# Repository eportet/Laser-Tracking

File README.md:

# Laser-Tracking

Code
====

Three folders in this directory:
* CameraTracking: Contains code that does corse tracking on RasPi
* Transmitter: Contains code that runs on photon plugged inito receiver PCBs
* Receiver: Contains code that runs on photon controlling servos and MEMS

Flashing Photon Code
====================

* Download Particle CLI on Mac or Linux. See Particle help for details.
* Place Photon in DFU mode by holding down both buttons, release Setup button. Light should blink purple, continue to hold the Reset button until light blinks yellow.
* Run ```particle photon compile --saveTo out.bin .``` in directory with *.ino file.
* Run ```particle flash --usb out.bin```
* When program is running, particle light should be constant white. If the light blinks green or blue, something is wrong, check that system mode is set to manual in code and that photon firmware is up to date.

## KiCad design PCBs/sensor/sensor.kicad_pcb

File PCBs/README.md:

# PCBs for laser tracking
We've got two PCBs to make the sensor for the drone.
The **sensor** board holds 24 photodiodes and sticks the info on a 26-pin header. The outputs require pullup resistors.
The **mux** board attaches to the sensor board, and is also designed to hold a particle photon and a RF communication module.

The kicad files, digikey bill of materials, and gerbers are in each of the directories. BOM for 3 boards + a spare, which is the minumum oshpark order.
We printed both boards with oshpark and it worked out well enough. "Sensor" is on 2oz copper, "mux" is standard.

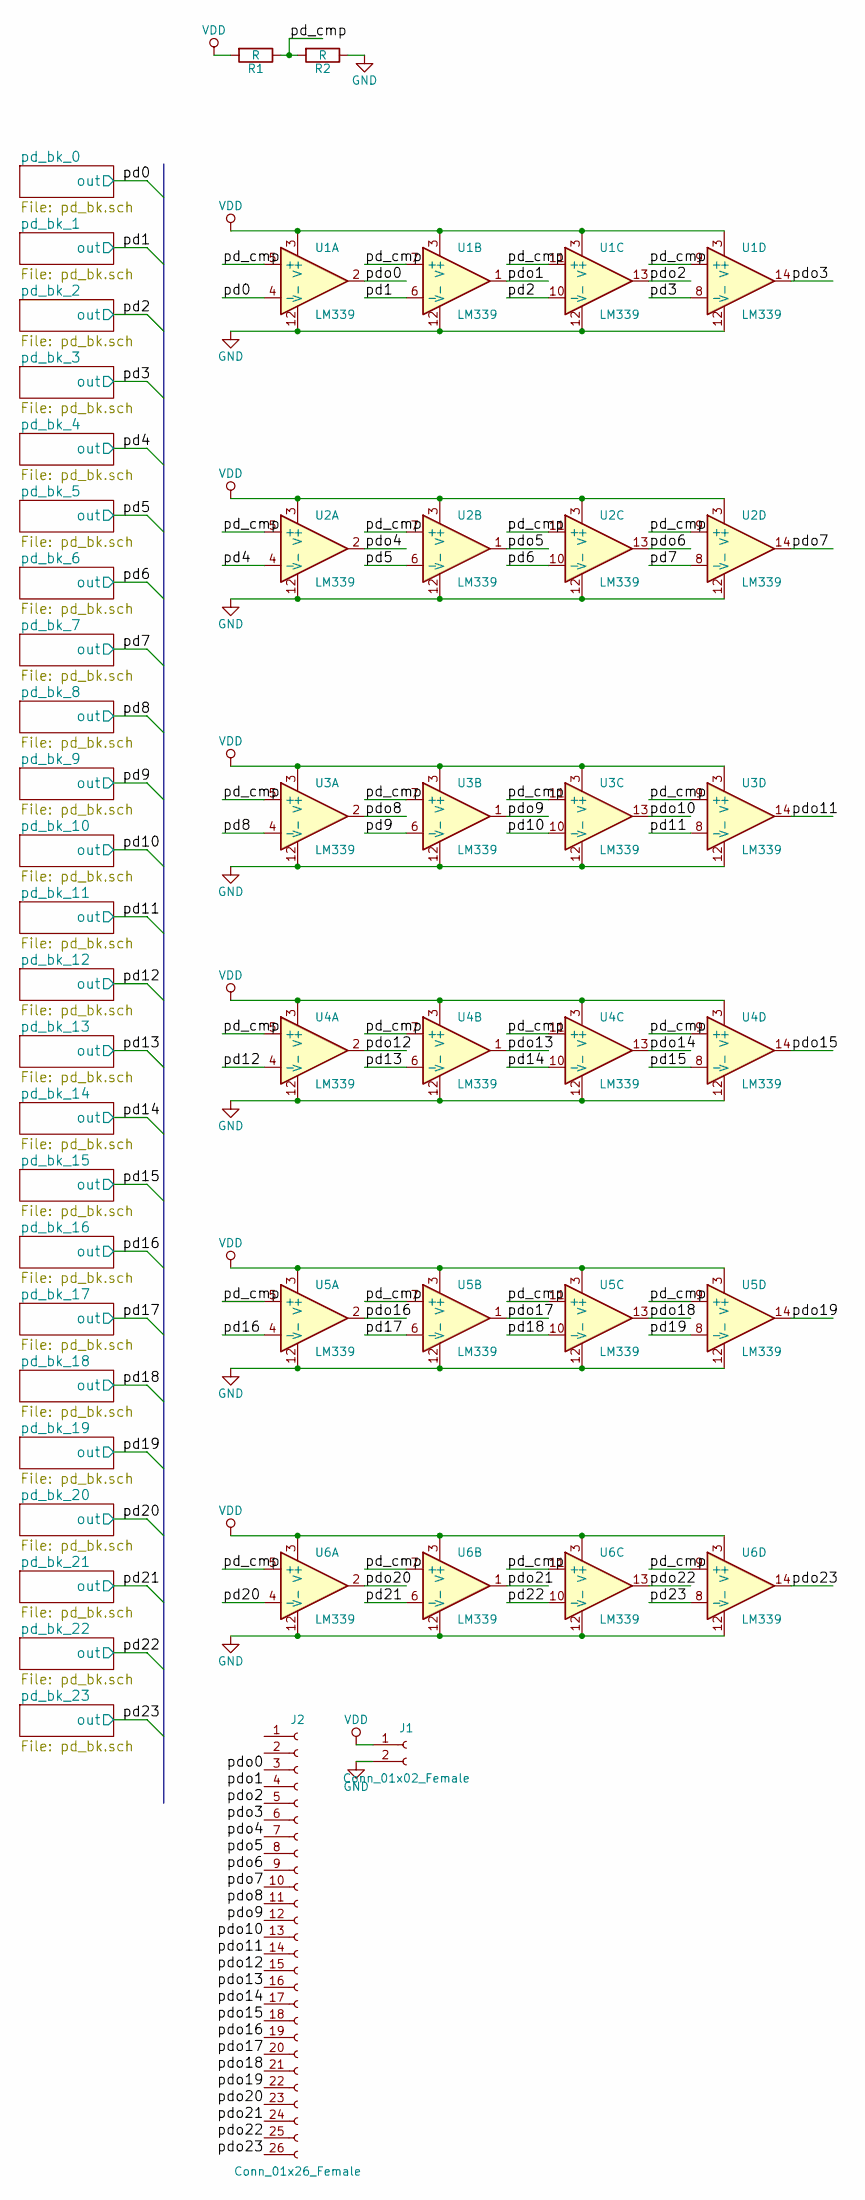
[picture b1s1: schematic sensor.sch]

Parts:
J1: Conn_01x02_Female; Pin_Header_Straight_1x02_Pitch2.54mm
J2: Conn_01x26_Female; Pin_Header_Straight_2x13_Pitch2.54mm
R1, R2: R; R_Axial_DIN0207_L6.3mm_D2.5mm_P2.54mm_Vertical
U1, U2, U3, U4, U5, U6: LM339; SOIC-14_3.9x8.7mm_Pitch1.27mm

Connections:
/pd0: U1.4 (-); also elsewhere on the board
/pd1: U1.6 (-); also elsewhere on the board
/pd2: U1.10 (-); also elsewhere on the board
/pd3: U1.8 (-); also elsewhere on the board
/pd4: U2.4 (-); also elsewhere on the board
/pd5: U2.6 (-); also elsewhere on the board
/pd6: U2.10 (-); also elsewhere on the board
/pd7: U2.8 (-); also elsewhere on the board
/pd8: U3.4 (-); also elsewhere on the board
/pd9: U3.6 (-); also elsewhere on the board
/pd10: U3.10 (-); also elsewhere on the board
/pd11: U3.8 (-); also elsewhere on the board
/pd12: U4.4 (-); also elsewhere on the board
/pd13: U4.6 (-); also elsewhere on the board
/pd14: U4.10 (-); also elsewhere on the board
/pd15: U4.8 (-); also elsewhere on the board
/pd16: U5.4 (-); also elsewhere on the board
/pd17: U5.6 (-); also elsewhere on the board
/pd18: U5.10 (-); also elsewhere on the board
/pd19: U5.8 (-); also elsewhere on the board
/pd20: U6.4 (-); also elsewhere on the board
/pd21: U6.6 (-); also elsewhere on the board
/pd22: U6.10 (-); also elsewhere on the board
/pd23: U6.8 (-); also elsewhere on the board
/pd_cmp: R1.1, R2.2, U1.5 (+), U1.7 (+), U1.9 (+), U1.11 (+), U2.5 (+), U2.7 (+), U2.9 (+), U2.11 (+), U3.5 (+), U3.7 (+), U3.9 (+), U3.11 (+), U4.5 (+), U4.7 (+), U4.9 (+), U4.11 (+), U5.5 (+), U5.7 (+), U5.9 (+), U5.11 (+), U6.5 (+), U6.7 (+), U6.9 (+), U6.11 (+)
/pdo0: J2.3, U1.2
/pdo1: J2.4, U1.1
/pdo2: J2.5, U1.13
/pdo3: J2.6, U1.14
/pdo4: J2.7, U2.2
/pdo5: J2.8, U2.1
/pdo6: J2.9, U2.13
/pdo7: J2.10, U2.14
/pdo8: J2.11, U3.2
/pdo9: J2.12, U3.1
/pdo10: J2.13, U3.13
/pdo11: J2.14, U3.14
/pdo12: J2.15, U4.2
/pdo13: J2.16, U4.1
/pdo14: J2.17, U4.13
/pdo15: J2.18, U4.14
/pdo16: J2.19, U5.2
/pdo17: J2.20, U5.1
/pdo18: J2.21, U5.13
/pdo19: J2.22, U5.14
/pdo20: J2.23, U6.2
/pdo21: J2.24, U6.1
/pdo22: J2.25, U6.13
/pdo23: J2.26, U6.14
GND: J1.2, R2.1, U1.12 (V-), U2.12 (V-), U3.12 (V-), U4.12 (V-), U5.12 (V-), U6.12 (V-); also elsewhere on the board
VDD: J1.1, R1.2, U1.3 (V+), U2.3 (V+), U3.3 (V+), U4.3 (V+), U5.3 (V+), U6.3 (V+); also elsewhere on the board

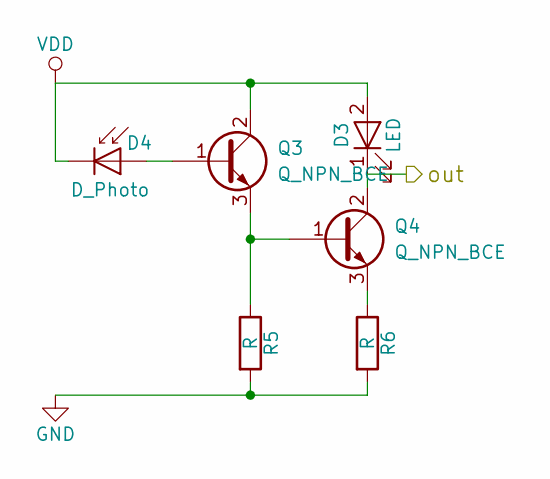
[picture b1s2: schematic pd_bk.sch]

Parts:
D1: LED; LED_1206_HandSoldering
D2: D_Photo; LED_1206
Q1, Q2: Q_NPN_BCE; SOT-23_Handsoldering
R3, R4: R; R_1206_HandSoldering

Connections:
/pd0: D1.1 (K), Q2.2 (C); also elsewhere on the board
GND: R3.2, R4.2; also elsewhere on the board
unnamed: D2.2 (A), Q1.1 (B)
unnamed: Q1.3 (E), Q2.1 (B), R3.1
unnamed: Q2.3 (E), R4.1
VDD: D1.2 (A), D2.1 (K), Q1.2 (C); also elsewhere on the board

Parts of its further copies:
D3, D5, D7, D9, D11, D13, D15, D17, D19, D21, D23, D25, D27, D29, D31, D33, D35, D37, D39, D41, D43, D45, D47, D49: LED; LED_1206_HandSoldering
D4, D6, D8, D10, D12, D14, D16, D18, D20, D22, D24, D26, D28, D30, D32, D34, D36, D38, D40, D42, D44, D46, D48, D50: D_Photo; LED_1206
Q3, Q4, Q5, Q6, Q7, Q8, Q9, Q10, Q11, Q12, Q13, Q14, Q15, Q16, Q17, Q18, Q19, Q20, Q21, Q22, Q23, Q24, Q25, Q26, Q27, Q28, Q29, Q30, Q31, Q32, Q33, Q34, Q35, Q36, Q37, Q38, Q39, Q40, Q41, Q42, Q43, Q44, Q45, Q46, Q47, Q48, Q49, Q50: Q_NPN_BCE; SOT-23_Handsoldering
R5, R6, R7, R8, R9, R10, R11, R12, R13, R14, R15, R16, R17, R18, R19, R20, R21, R22, R23, R24, R25, R26, R27, R28, R29, R30, R31, R32, R33, R34, R35, R36, R37, R38, R39, R40, R41, R42, R43, R44, R45, R46, R47, R48, R49, R50, R51, R52: R; R_1206_HandSoldering

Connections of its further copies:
/pd1: D3.1 (K), Q4.2 (C); also elsewhere on the board
/pd2: D5.1 (K), Q6.2 (C); also elsewhere on the board
/pd3: D7.1 (K), Q8.2 (C); also elsewhere on the board
/pd4: D9.1 (K), Q10.2 (C); also elsewhere on the board
/pd5: D11.1 (K), Q12.2 (C); also elsewhere on the board
/pd6: D13.1 (K), Q14.2 (C); also elsewhere on the board
/pd7: D15.1 (K), Q16.2 (C); also elsewhere on the board
/pd8: D17.1 (K), Q18.2 (C); also elsewhere on the board
/pd9: D19.1 (K), Q20.2 (C); also elsewhere on the board
/pd10: D21.1 (K), Q22.2 (C); also elsewhere on the board
/pd11: D23.1 (K), Q24.2 (C); also elsewhere on the board
/pd12: D25.1 (K), Q26.2 (C); also elsewhere on the board
/pd13: D27.1 (K), Q28.2 (C); also elsewhere on the board
/pd14: D29.1 (K), Q30.2 (C); also elsewhere on the board
/pd15: D31.1 (K), Q32.2 (C); also elsewhere on the board
/pd16: D33.1 (K), Q34.2 (C); also elsewhere on the board
/pd17: D35.1 (K), Q36.2 (C); also elsewhere on the board
/pd18: D37.1 (K), Q38.2 (C); also elsewhere on the board
/pd19: D39.1 (K), Q40.2 (C); also elsewhere on the board
/pd20: D41.1 (K), Q42.2 (C); also elsewhere on the board
/pd21: D43.1 (K), Q44.2 (C); also elsewhere on the board
/pd22: D45.1 (K), Q46.2 (C); also elsewhere on the board
/pd23: D47.1 (K), Q48.2 (C); also elsewhere on the board
GND: R5.2, R6.2, R7.2, R8.2, R9.2, R10.2, R11.2, R12.2, R13.2, R14.2, R15.2, R16.2, R17.2, R18.2, R19.2, R20.2, R21.2, R22.2, R23.2, R24.2, R25.2, R26.2, R27.2, R28.2, R29.2, R30.2, R31.2, R32.2, R33.2, R34.2, R35.2, R36.2, R37.2, R38.2, R39.2, R40.2, R41.2, R42.2, R43.2, R44.2, R45.2, R46.2, R47.2, R48.2, R49.2, R50.2; also elsewhere on the board
unnamed: D4.2 (A), Q3.1 (B)
unnamed: D6.2 (A), Q5.1 (B)
unnamed: D8.2 (A), Q7.1 (B)
unnamed: D10.2 (A), Q9.1 (B)
unnamed: D12.2 (A), Q11.1 (B)
unnamed: D14.2 (A), Q13.1 (B)
unnamed: D16.2 (A), Q15.1 (B)
unnamed: D18.2 (A), Q17.1 (B)
unnamed: D20.2 (A), Q19.1 (B)
unnamed: D22.2 (A), Q21.1 (B)
unnamed: D24.2 (A), Q23.1 (B)
unnamed: D26.2 (A), Q25.1 (B)
unnamed: D28.2 (A), Q27.1 (B)
unnamed: D30.2 (A), Q29.1 (B)
unnamed: D32.2 (A), Q31.1 (B)
unnamed: D34.2 (A), Q33.1 (B)
unnamed: D36.2 (A), Q35.1 (B)
unnamed: D38.2 (A), Q37.1 (B)
unnamed: D40.2 (A), Q39.1 (B)
unnamed: D42.2 (A), Q41.1 (B)
unnamed: D44.2 (A), Q43.1 (B)
unnamed: D46.2 (A), Q45.1 (B)
unnamed: D48.2 (A), Q47.1 (B)
unnamed: Q3.3 (E), Q4.1 (B), R5.1
unnamed: Q4.3 (E), R6.1
unnamed: Q5.3 (E), Q6.1 (B), R7.1
unnamed: Q6.3 (E), R8.1
unnamed: Q7.3 (E), Q8.1 (B), R9.1
unnamed: Q8.3 (E), R10.1
unnamed: Q9.3 (E), Q10.1 (B), R11.1
unnamed: Q10.3 (E), R12.1
unnamed: Q11.3 (E), Q12.1 (B), R13.1
unnamed: Q12.3 (E), R14.1
unnamed: Q13.3 (E), Q14.1 (B), R15.1
unnamed: Q14.3 (E), R16.1
unnamed: Q15.3 (E), Q16.1 (B), R17.1
unnamed: Q16.3 (E), R18.1
unnamed: Q17.3 (E), Q18.1 (B), R19.1
unnamed: Q18.3 (E), R20.1
unnamed: Q19.3 (E), Q20.1 (B), R21.1
unnamed: Q20.3 (E), R22.1
unnamed: Q21.3 (E), Q22.1 (B), R23.1
unnamed: Q22.3 (E), R24.1
unnamed: Q23.3 (E), Q24.1 (B), R25.1
unnamed: Q24.3 (E), R26.1
unnamed: Q25.3 (E), Q26.1 (B), R27.1
unnamed: Q26.3 (E), R28.1
unnamed: Q27.3 (E), Q28.1 (B), R29.1
unnamed: Q28.3 (E), R30.1
unnamed: Q29.3 (E), Q30.1 (B), R31.1
unnamed: Q30.3 (E), R32.1
unnamed: Q31.3 (E), Q32.1 (B), R33.1
unnamed: Q32.3 (E), R34.1
unnamed: Q33.3 (E), Q34.1 (B), R35.1
unnamed: Q34.3 (E), R36.1
unnamed: Q35.3 (E), Q36.1 (B), R37.1
unnamed: Q36.3 (E), R38.1
unnamed: Q37.3 (E), Q38.1 (B), R39.1
unnamed: Q38.3 (E), R40.1
unnamed: Q39.3 (E), Q40.1 (B), R41.1
unnamed: Q40.3 (E), R42.1
unnamed: Q41.3 (E), Q42.1 (B), R43.1
unnamed: Q42.3 (E), R44.1
unnamed: Q43.3 (E), Q44.1 (B), R45.1
unnamed: Q44.3 (E), R46.1
unnamed: Q45.3 (E), Q46.1 (B), R47.1
unnamed: Q46.3 (E), R48.1
unnamed: Q47.3 (E), Q48.1 (B), R49.1
unnamed: Q48.3 (E), R50.1
VDD: D3.2 (A), D4.1 (K), D5.2 (A), D6.1 (K), D7.2 (A), D8.1 (K), D9.2 (A), D10.1 (K), D11.2 (A), D12.1 (K), D13.2 (A), D14.1 (K), D15.2 (A), D16.1 (K), D17.2 (A), D18.1 (K), D19.2 (A), D20.1 (K), D21.2 (A), D22.1 (K), D23.2 (A), D24.1 (K), D25.2 (A), D26.1 (K), D27.2 (A), D28.1 (K), D29.2 (A), D30.1 (K), D31.2 (A), D32.1 (K), D33.2 (A), D34.1 (K), D35.2 (A), D36.1 (K), D37.2 (A), D38.1 (K), D39.2 (A), D40.1 (K), D41.2 (A), D42.1 (K), D43.2 (A), D44.1 (K), D45.2 (A), D46.1 (K), D47.2 (A), D48.1 (K), Q3.2 (C), Q5.2 (C), Q7.2 (C), Q9.2 (C), Q11.2 (C), Q13.2 (C), Q15.2 (C), Q17.2 (C), Q19.2 (C), Q21.2 (C), Q23.2 (C), Q25.2 (C), Q27.2 (C), Q29.2 (C), Q31.2 (C), Q33.2 (C), Q35.2 (C), Q37.2 (C), Q39.2 (C), Q41.2 (C), Q43.2 (C), Q45.2 (C), Q47.2 (C); also elsewhere on the board

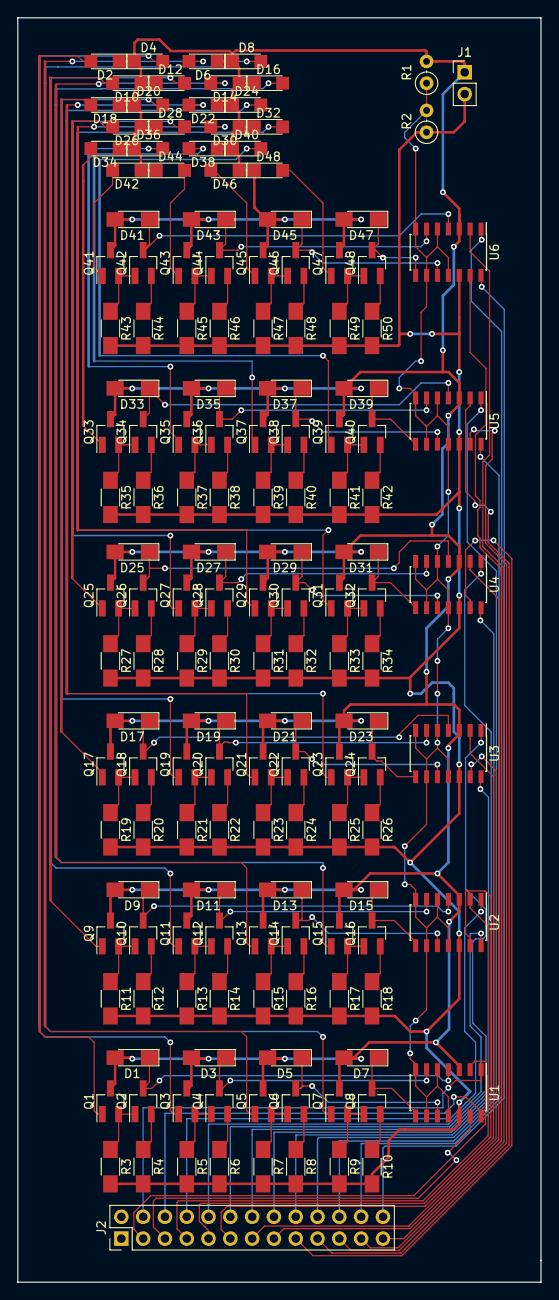
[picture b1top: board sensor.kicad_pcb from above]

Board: 2 copper layers, 61.0 x 147.3 mm, 154 parts (0 on the bottom side), 123 nets.

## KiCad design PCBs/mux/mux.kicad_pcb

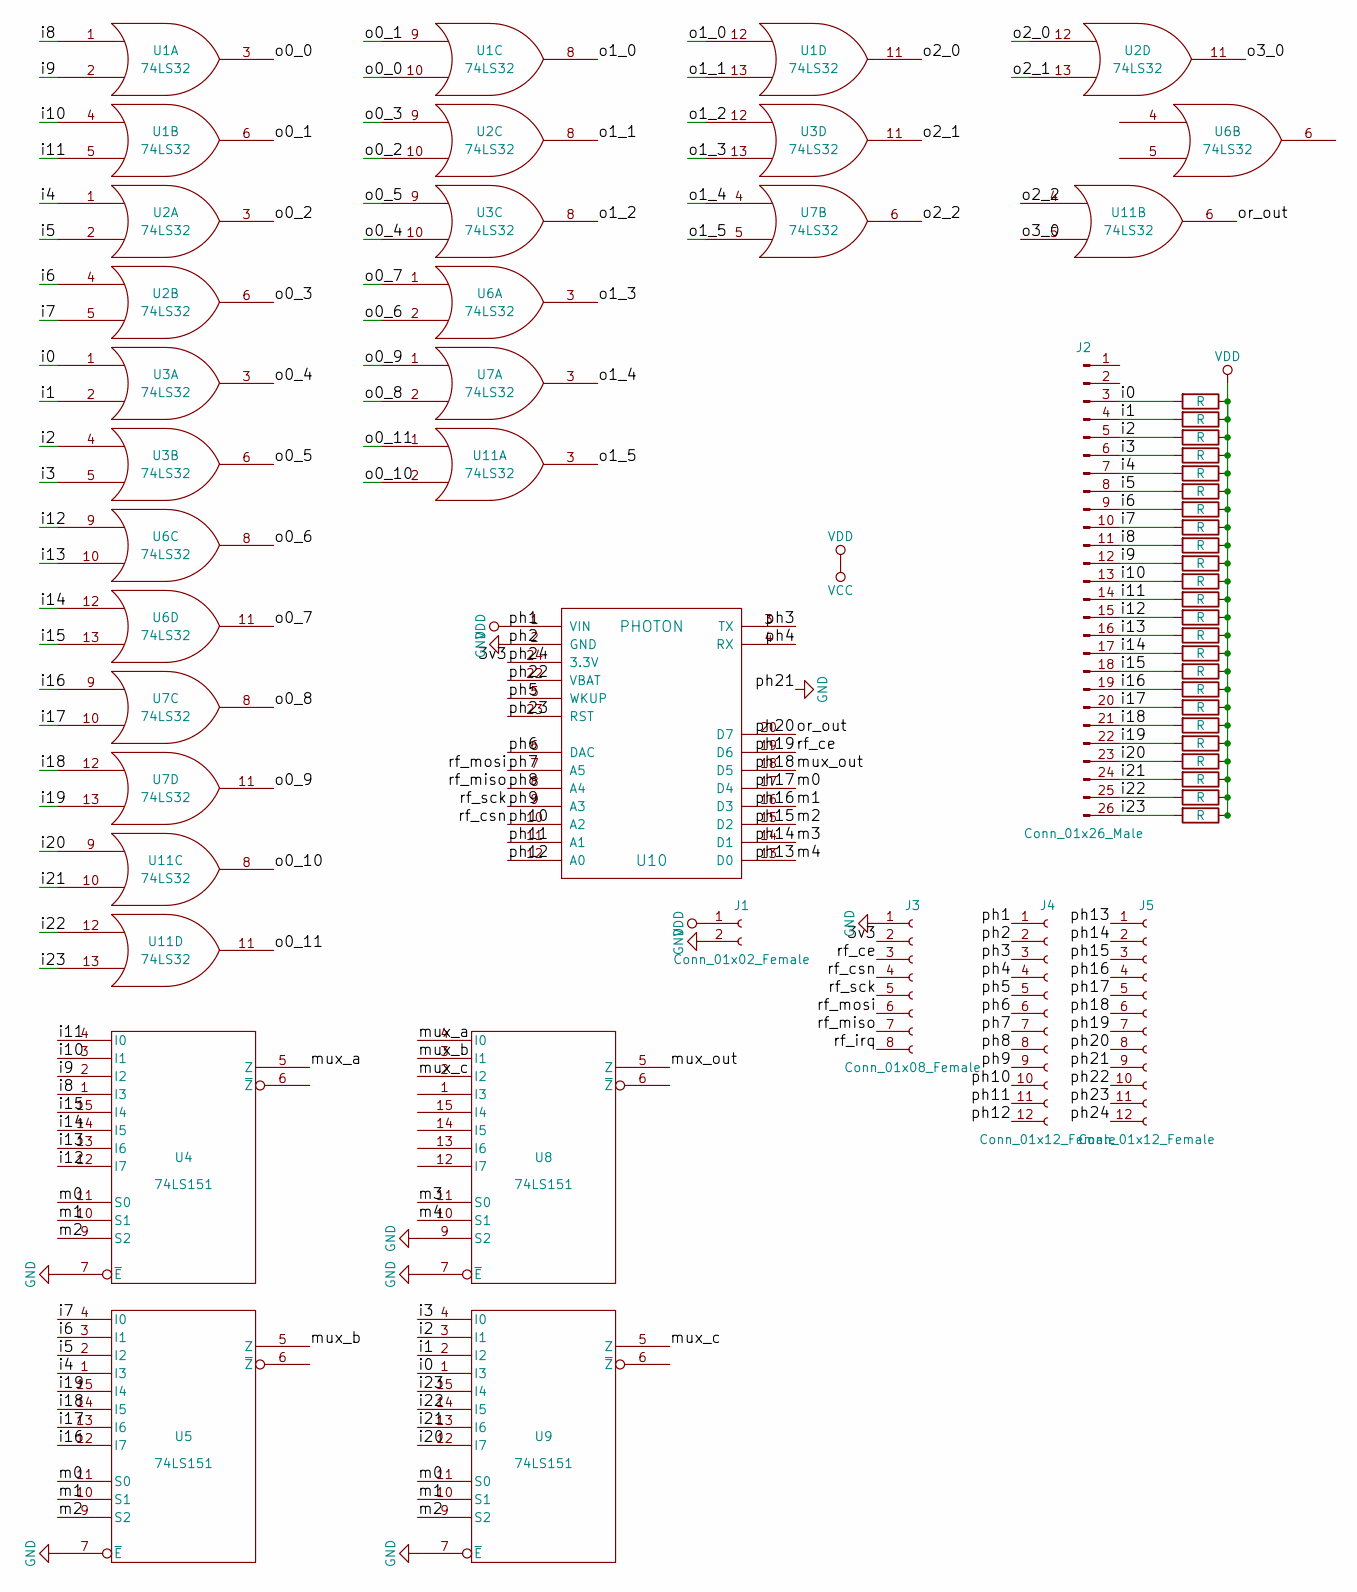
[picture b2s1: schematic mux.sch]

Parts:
J1: Conn_01x02_Female; Pin_Header_Straight_1x02_Pitch2.54mm
J2: Conn_01x26_Male; Pin_Header_Straight_2x13_Pitch2.54mm
J3: Conn_01x08_Female; Pin_Header_Straight_2x04_Pitch2.54mm
J4, J5: Conn_01x12_Female; Pin_Header_Straight_1x12_Pitch2.54mm
R1, R2, R3, R4, R5, R6, R7, R8, R9, R10, R11, R12, R13, R14, R15, R16, R17, R18, R19, R20, R21, R22, R23, R24: R; R_1206
U1, U2, U3, U6, U7, U11: 74LS32; SOIC-14_3.9x8.7mm_Pitch1.27mm
U4, U5, U8, U9: 74LS151; SOIC-16_3.9x9.9mm_Pitch1.27mm
U10: PHOTON

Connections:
/3v3: J3.2, J5.12, U10.24 (3.3V)
/i0: J2.3, R1.2, U3.1, U9.1 (I3)
/i1: J2.4, R2.2, U3.2, U9.2 (I2)
/i2: J2.5, R3.2, U3.4, U9.3 (I1)
/i3: J2.6, R4.2, U3.5, U9.4 (I0)
/i4: J2.7, R5.2, U2.1, U5.1 (I3)
/i5: J2.8, R6.2, U2.2, U5.2 (I2)
/i6: J2.9, R7.2, U2.4, U5.3 (I1)
/i7: J2.10, R8.2, U2.5, U5.4 (I0)
/i8: J2.11, R9.2, U1.1, U4.1 (I3)
/i9: J2.12, R10.2, U1.2, U4.2 (I2)
/i10: J2.13, R11.2, U1.4, U4.3 (I1)
/i11: J2.14, R12.2, U1.5, U4.4 (I0)
/i12: J2.15, R13.2, U4.12 (I7), U6.9
/i13: J2.16, R14.2, U4.13 (I6), U6.10
/i14: J2.17, R15.2, U4.14 (I5), U6.12
/i15: J2.18, R16.2, U4.15 (I4), U6.13
/i16: J2.19, R17.2, U5.12 (I7), U7.9
/i17: J2.20, R18.2, U5.13 (I6), U7.10
/i18: J2.21, R19.2, U5.14 (I5), U7.12
/i19: J2.22, R20.2, U5.15 (I4), U7.13
/i20: J2.23, R21.2, U9.12 (I7), U11.9
/i21: J2.24, R22.2, U9.13 (I6), U11.10
/i22: J2.25, R23.2, U9.14 (I5), U11.12
/i23: J2.26, R24.2, U9.15 (I4), U11.13
/m0: J5.5, U4.11 (S0), U5.11 (S0), U9.11 (S0), U10.17 (D4)
/m1: J5.4, U4.10 (S1), U5.10 (S1), U9.10 (S1), U10.16 (D3)
/m2: J5.3, U4.9 (S2), U5.9 (S2), U9.9 (S2), U10.15 (D2)
/m3: J5.2, U8.11 (S0), U10.14 (D1)
/m4: J5.1, U8.10 (S1), U10.13 (D0)
/mux_a: U4.5 (Z), U8.4 (I0)
/mux_b: U5.5 (Z), U8.3 (I1)
/mux_c: U8.2 (I2), U9.5 (Z)
/mux_out: J5.6, U8.5 (Z), U10.18 (D5)
/o0_0: U1.3, U1.10
/o0_1: U1.6, U1.9
/o0_2: U2.3, U2.10
/o0_3: U2.6, U2.9
/o0_4: U3.3, U3.10
/o0_5: U3.6, U3.9
/o0_6: U6.2, U6.8
/o0_7: U6.1, U6.11
/o0_8: U7.2, U7.8
/o0_9: U7.1, U7.11
/o0_10: U11.2, U11.8
/o0_11: U11.1, U11.11
/o1_0: U1.8, U1.12
/o1_1: U1.13, U2.8
/o1_2: U3.8, U3.12
/o1_3: U3.13, U6.3
/o1_4: U7.3, U7.4
/o1_5: U7.5, U11.3
/o2_0: U1.11, U2.12
/o2_1: U2.13, U3.11
/o2_2: U7.6, U11.4
/o3_0: U2.11, U11.5
/or_out: J5.8, U10.20 (D7), U11.6
/ph3: J4.3, U10.3 (TX)
/ph4: J4.4, U10.4 (RX)
/ph5: J4.5, U10.5 (WKUP)
/ph6: J4.6, U10.6 (DAC)
/ph7: J3.6, J4.7, U10.7 (A5)
/ph8: J3.7, J4.8, U10.8 (A4)
/ph9: J3.5, J4.9, U10.9 (A3)
/ph10: J3.4, J4.10, U10.10 (A2)
/ph11: J4.11, U10.11 (A1)
/ph12: J4.12, U10.12 (A0)
/ph19: J3.3, J5.7, U10.19 (D6)
/ph22: J5.10, U10.22 (VBAT)
/ph23: J5.11, U10.23 (RST)
/rf_irq: J3.8
GND: J1.2, J3.1, J4.2, J5.9, U1.7 (GND), U2.7 (GND), U3.7 (GND), U4.7 (~E), U4.8 (GND), U5.7 (~E), U5.8 (GND), U6.7 (GND), U7.7 (GND), U8.7 (~E), U8.8 (GND), U8.9 (S2), U9.7 (~E), U9.8 (GND), U10.2 (GND), U11.7 (GND)
VCC: J1.1, J4.1, R1.1, R2.1, R3.1, R4.1, R5.1, R6.1, R7.1, R8.1, R9.1, R10.1, R11.1, R12.1, R13.1, R14.1, R15.1, R16.1, R17.1, R18.1, R19.1, R20.1, R21.1, R22.1, R23.1, R24.1, U1.14 (VCC), U2.14 (VCC), U3.14 (VCC), U4.16 (VCC), U5.16 (VCC), U6.14 (VCC), U7.14 (VCC), U8.16 (VCC), U9.16 (VCC), U10.1 (VIN), U11.14 (VCC)

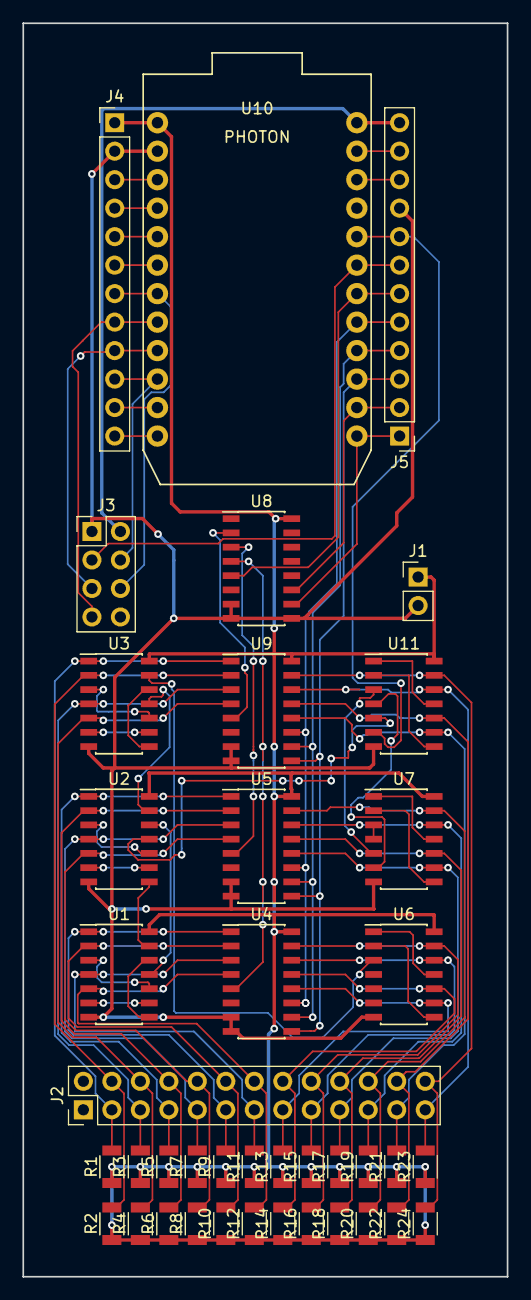
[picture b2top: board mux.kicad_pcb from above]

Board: 2 copper layers, 43.2 x 111.8 mm, 41 parts (1 on the bottom side), 72 nets.

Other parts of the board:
LOGO: LOGO

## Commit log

2018-02-11 First Commit with base Transmitter Receiver Arduino Code
2018-02-11 Adding Photon Code for controlling MEMS Mirror
2018-03-20 Working color tracking and serial communication with Photon
2018-03-20 Serial communication failsafe
2018-03-20 Added particle tracking code and revised transmitter code for new array.
2018-03-20 Deleted old directories
2018-03-24 Updated with servo code.
2018-03-24 I think this is a PID controller
2018-03-24 will this work?
2018-03-25 Added NRF pin out image
2018-03-27 Servo controller working
2018-03-28 cleaner coarse tracking (servo mechanism needs testing with a diff power supply)
2018-04-02 format fix
2018-04-18 temporary commit
2018-04-24 Add files via upload
    Some Lidar Stuff added
2018-04-29 Add PCBs
2018-04-29 Some of the Lidar stuff which isn't completely done added
2018-04-30 Add Submitted Documents
2018-04-30 Reorganized fiel structure. Removed extraneous files.
2018-04-30 Added README
2018-04-30 hardware report PCBs v1
2018-04-30 Add layout photos
2018-04-30 Added STL files for mechanical components.
2018-05-02 Update to Reciever side and Transmitter side code. First Working commit with particle on Transmitter.
2018-05-03 update coarse
2018-05-03 Serial communication 'UDLR', servo movement deleted
2018-05-03 transformed dc values to milliseconds and write to serial
2018-05-04 ece day last minute
